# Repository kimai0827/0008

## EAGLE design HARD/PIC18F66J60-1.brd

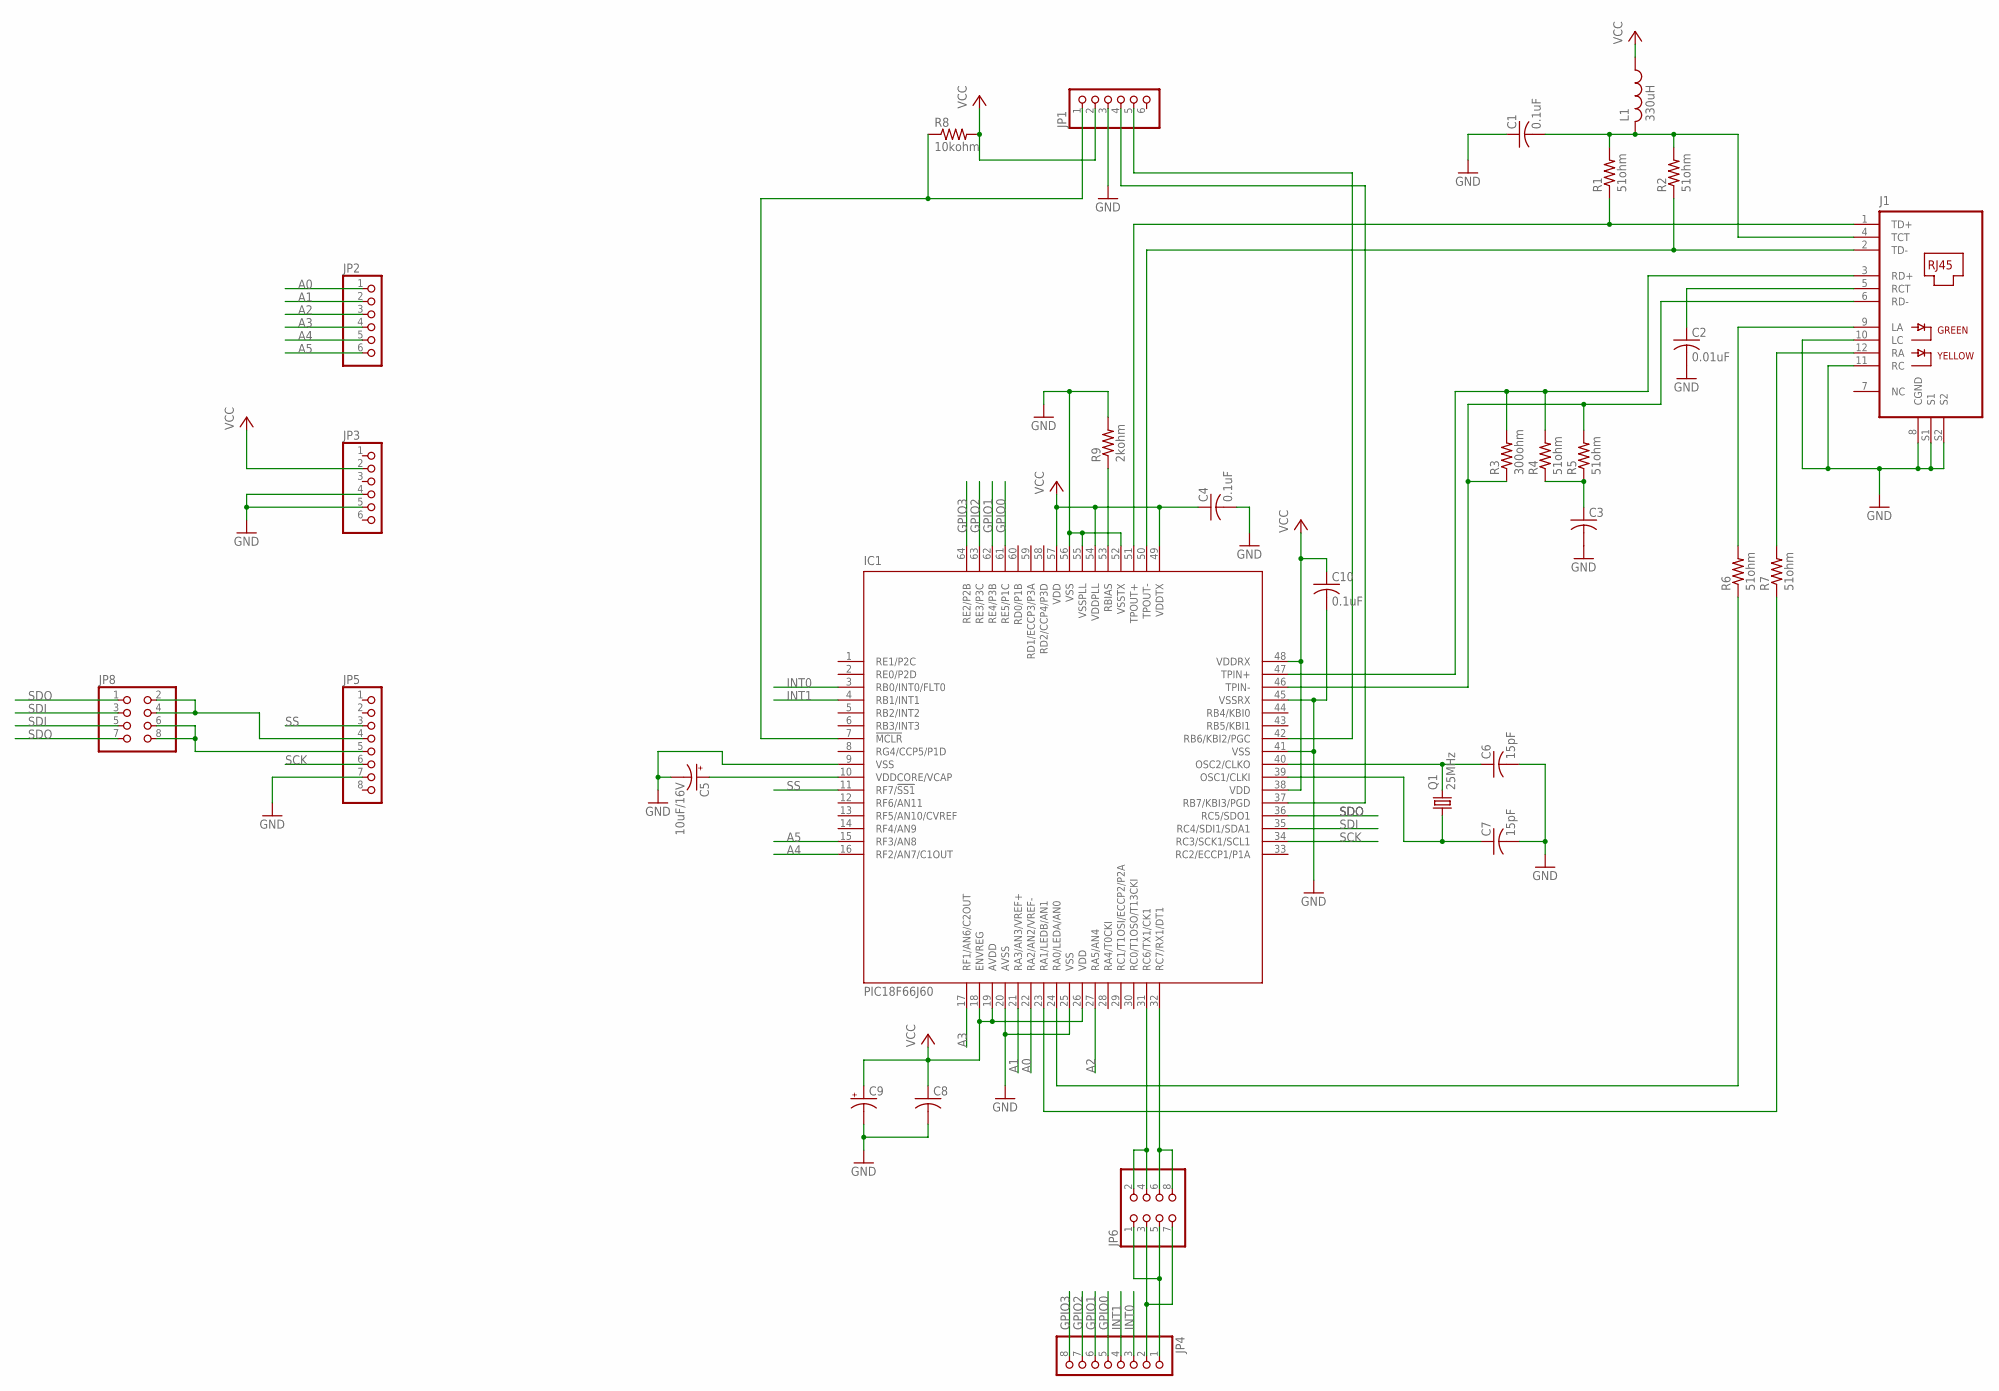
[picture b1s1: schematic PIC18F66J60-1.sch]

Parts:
C1, C4, C10: 0.1uF; C025-040X050
C2: 0.01uF; C025-040X050
C3, C8: C-US025-040X050; C025-040X050
C5: 10uF/16V; E2,5-7
C6, C7: 15pF; C025-040X050
C9: CPOL-USE2.5-7; E2,5-7
IC1: PIC18F66J60; TQFP64-10X10
J1: J0011; PJ-J0
JP1, JP2, JP3: PINHD-1X6; 1X06
JP4, JP5: PINHD-1X8; 1X08
JP6, JP8: PINHD-2X4; 2X04
L1: 330uH; 0204V
Q1: 25MHz; HC49/S
R1, R2, R4, R5, R6, R7: 51ohm; 0204V
R3: 300ohm; 0204V
R8: 10kohm; 0204V
R9: 2kohm; 0204V

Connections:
A0: IC1.22 (RA2/AN2/VREF-), JP2.1
A1: IC1.21 (RA3/AN3/VREF+), JP2.2
A2: IC1.27 (RA5/AN4), JP2.3
A3: IC1.17 (RF1/AN6/C2OUT), JP2.4
A4: IC1.16 (RF2/AN7/C1OUT), JP2.5
A5: IC1.15 (RF3/AN8), JP2.6
GND: C1.1, C2.2, C3.2, C4.2, C5.-, C6.2, C7.2, C8.2, C9.-, C10.2, IC1.9 (VSS), IC1.20 (AVSS), IC1.25 (VSS), IC1.41 (VSS), IC1.45 (VSSRX), IC1.52 (VSSTX), IC1.55 (VSSPLL), IC1.56 (VSS), J1.8 (CGND), J1.10 (LC), J1.11 (RC), J1.S1, J1.S2, JP1.3, JP3.4, JP3.5, JP5.7, R9.2
GPIO0: IC1.61 (RE5/P1C), JP4.5
GPIO1: IC1.62 (RE4/P3B), JP4.6
GPIO2: IC1.63 (RE3/P3C), JP4.7
GPIO3: IC1.64 (RE2/P2B), JP4.8
INT0: IC1.3 (RB0/INT0/FLT0), JP4.3
INT1: IC1.4 (RB1/INT1), JP4.4
unnamed: IC1.51 (TPOUT+), J1.1 (TD+), R1.1
unnamed: IC1.50 (TPOUT-), J1.2 (TD-), R2.1
unnamed: C1.2, J1.4 (TCT), L1.2, R1.2, R2.2
unnamed: IC1.47 (TPIN+), J1.3 (RD+), R3.2, R4.2
unnamed: IC1.46 (TPIN-), J1.6 (RD-), R3.1, R5.2
unnamed: C2.1, J1.5 (RCT)
unnamed: C3.1, R4.1, R5.1
unnamed: J1.9 (LA), R6.2
unnamed: J1.12 (RA), R7.2
unnamed: IC1.37 (RB7/KBI3/PGD), JP1.4
unnamed: IC1.7 (!MCLR), JP1.1, R8.1
unnamed: IC1.24 (RA0/LEDA/AN0), R6.1
unnamed: IC1.23 (RA1/LEDB/AN1), R7.1
unnamed: IC1.42 (RB6/KBI2/PGC), JP1.5
unnamed: C6.1, IC1.40 (OSC2/CLKO), Q1.2
unnamed: C7.1, IC1.39 (OSC1/CLKI), Q1.1
unnamed: IC1.31 (RC6/TX1/CK1), JP6.2, JP6.4
unnamed: IC1.53 (RBIAS), R9.1
unnamed: C5.+, IC1.10 (VDDCORE/VCAP)
unnamed: IC1.32 (RC7/RX1/DT1), JP6.6, JP6.8
unnamed: JP5.5, JP8.6, JP8.8
unnamed: JP4.2, JP6.3, JP6.7
unnamed: JP4.1, JP6.1, JP6.5
unnamed: JP5.4, JP8.2, JP8.4
SCK: IC1.34 (RC3/SCK1/SCL1), JP5.6
SDI: IC1.35 (RC4/SDI1/SDA1), JP8.3, JP8.5
SDO: IC1.36 (RC5/SDO1), JP8.1, JP8.7
SS: IC1.11 (RF7/!SS1), JP5.3
VCC: C4.1, C8.1, C9.+, C10.1, IC1.18 (ENVREG), IC1.19 (AVDD), IC1.26 (VDD), IC1.38 (VDD), IC1.48 (VDDRX), IC1.49 (VDDTX), IC1.54 (VDDPLL), IC1.57 (VDD), JP1.2, JP3.2, L1.1, R8.2

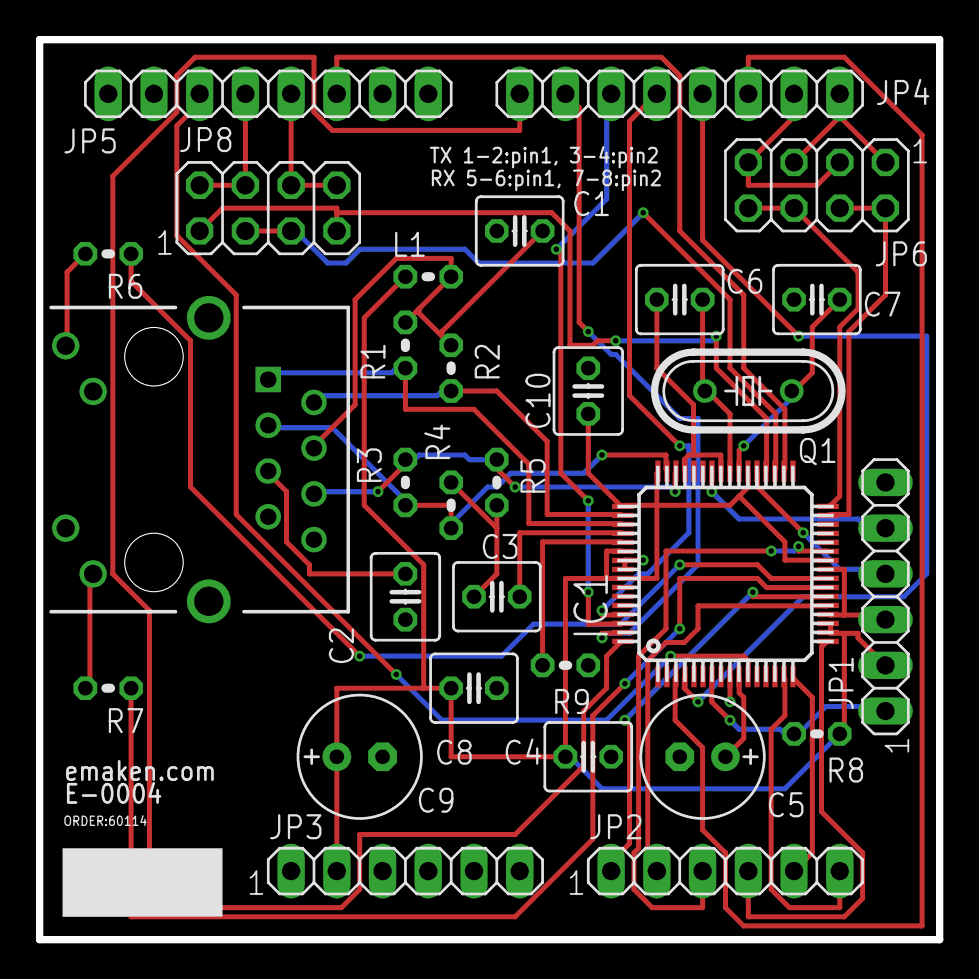
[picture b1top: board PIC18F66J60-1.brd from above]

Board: 2 copper layers, 50.0 x 50.0 mm, 30 parts (0 on the bottom side), 42 nets.

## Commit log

2012-11-06 initial release
